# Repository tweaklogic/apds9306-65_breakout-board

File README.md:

## Avago (Broadcom) APDS9306-65 Ambient Light Sensor

### Linux Kernel driver
- A Linux kernel driver for APDS9306 is available from kernel version 6.10 onwards.
- A backport of the driver for older kernel versions can be found [here](https://github.com/tweaklogic/apds9306_backport).

### LICENSE
Please refer to [LICENSE](https://github.com/tweaklogic/apds9306-65_breakout-board/blob/main/LICENSE) file in this repo.

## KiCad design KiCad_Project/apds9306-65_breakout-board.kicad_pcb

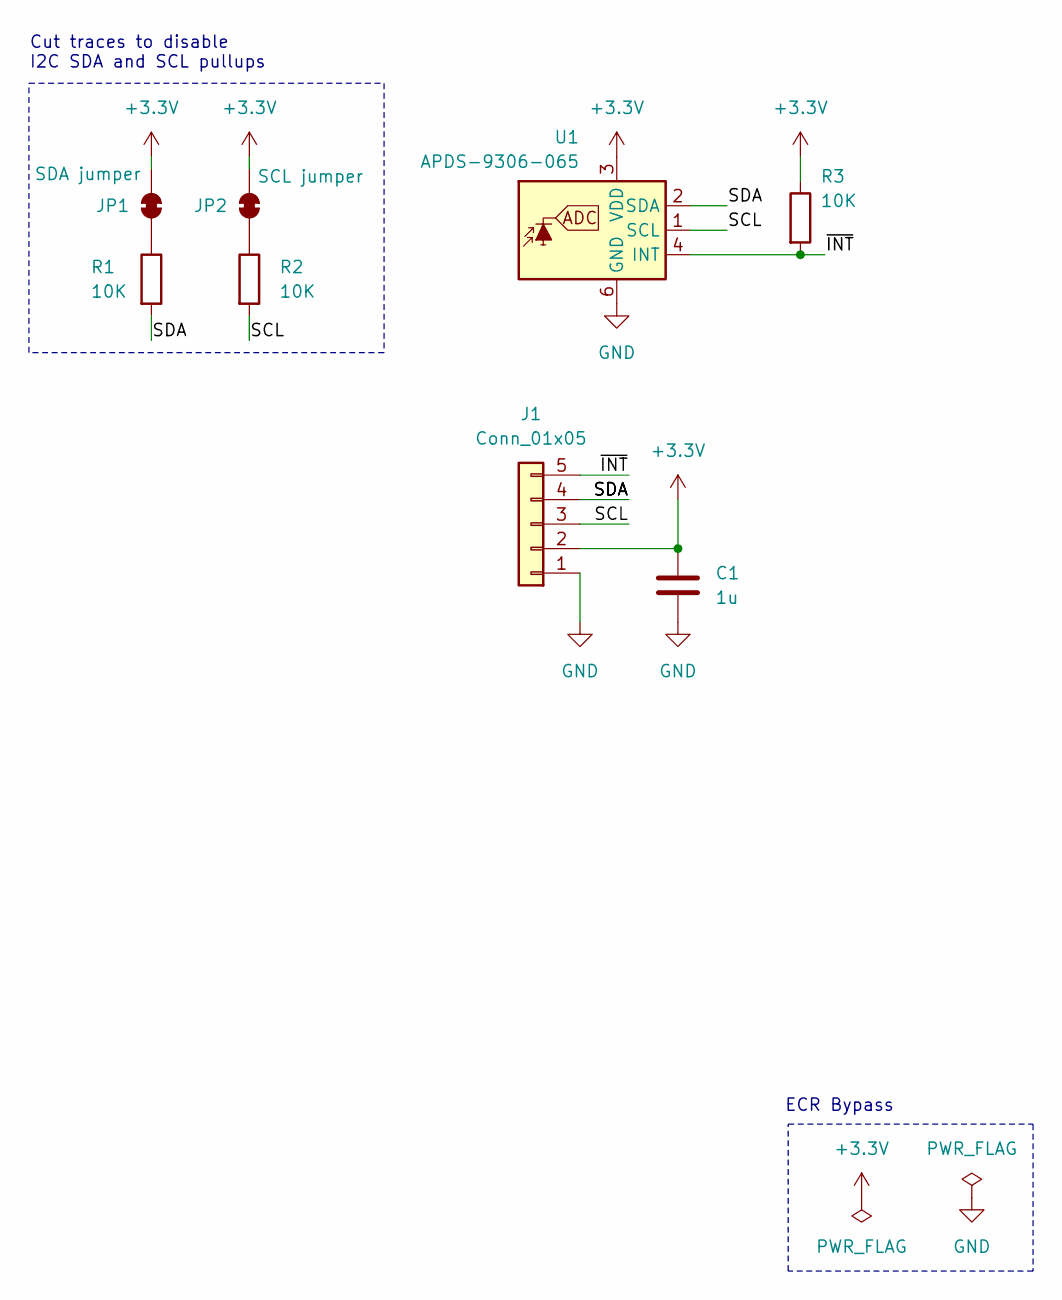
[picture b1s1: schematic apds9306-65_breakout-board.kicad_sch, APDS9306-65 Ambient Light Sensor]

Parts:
C1: 1u; C_0402_1005Metric
J1: Conn_01x05; PinHeader_1x05_P2.54mm_Horizontal
JP1: SDA jumper; SolderJumper-2_P1.3mm_Bridged_Pad1.0x1.5mm
JP2: SCL jumper; SolderJumper-2_P1.3mm_Bridged_Pad1.0x1.5mm
R1, R2, R3: 10K; R_0402_1005Metric
U1: APDS-9306-065; Broadcom_DFN-6_2x2mm_P0.65mm

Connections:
+3.3V: C1.1, J1.2, JP1.2 (B), JP2.2 (B), R3.1, U1.3 (VDD)
/SCL: J1.3, R2.2, U1.1 (SCL)
/SDA: J1.4, R1.2, U1.2 (SDA)
/~INT: J1.5, R3.2, U1.4 (INT)
GND: C1.2, J1.1, U1.6 (GND)
unnamed: JP1.1 (A), R1.1
unnamed: JP2.1 (A), R2.1

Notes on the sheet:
Cut traces to disable I2C SDA and SCL pullups
ECR Bypass

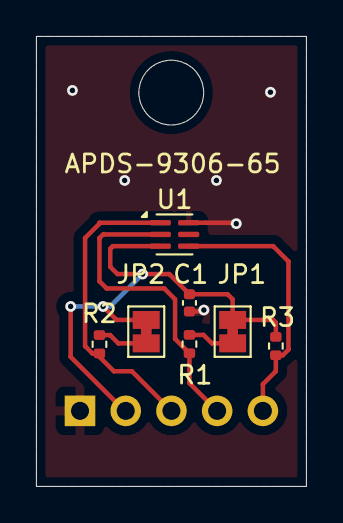
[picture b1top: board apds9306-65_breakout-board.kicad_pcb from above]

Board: 2 copper layers, 15.0 x 25.0 mm, 8 parts (1 on the bottom side), 7 nets.

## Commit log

2024-08-17 First commit of the project
    Add KiCad project, README and LICENSE.

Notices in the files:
KiCad_Project/apds9306-65_breakout-board.kicad_pcb:
License: https://creativecommons.org/licenses/by/4.0
